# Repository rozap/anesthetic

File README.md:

# anaesthetic
r a c i n g

## Libraries
* https://github.com/avishorp/TM1637
* https://github.com/rlogiacco/CircularBuffer
* [RadioHead](http://www.airspayce.com/mikem/arduino/RadioHead/) (see setup, below)

## Docs
Oil pressure sensor: autometer 2242 https://www.autometer.com/sensor_specs

## RadioHead setup
RadioHead is the library for the LoRa modules. It runs on Aduino boards.
We use RadioHead 1.116, modified to work on 915MHz (there's a call to setFrequency hardcoded in the library source). A pre-modified version is included in this repo. To setup, unzip `RadioHead-anesthetic.zip` to `$HOME/Arduino/libraries`.

## Radio range test
There is a pair of Arduino sketches for a basic radio range test in `radio_range_test`. See instructions in sketch comments.

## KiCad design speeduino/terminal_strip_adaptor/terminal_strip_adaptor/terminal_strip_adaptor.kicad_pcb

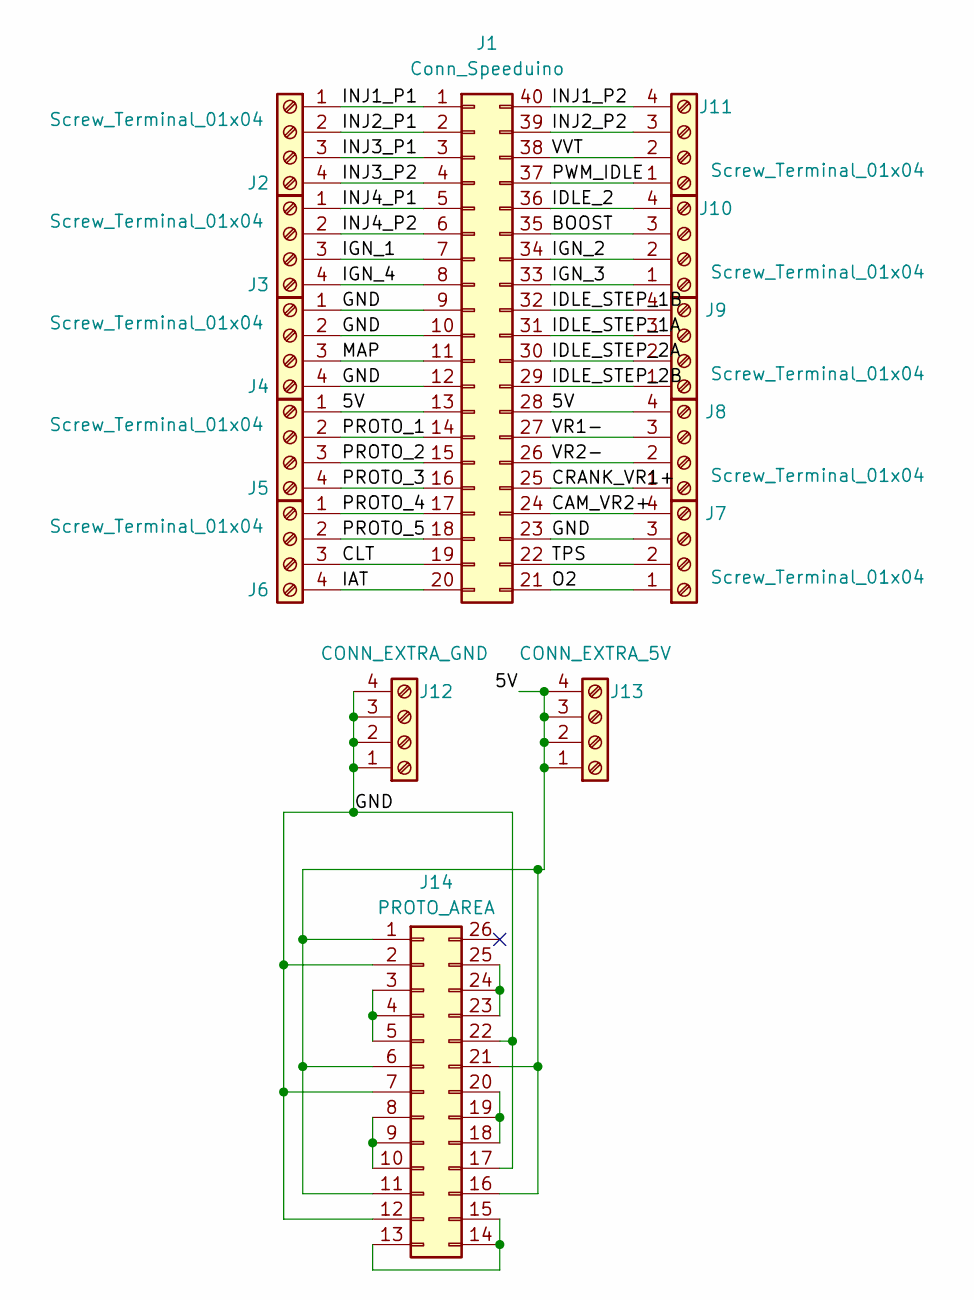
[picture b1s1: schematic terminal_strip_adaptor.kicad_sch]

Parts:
J1: Conn_Speeduino; PinSocket_2x20_P2.54mm_Vertical_CounterClockwise
J2, J3, J4, J5, J6, J7, J8, J9, J10, J11: Screw_Terminal_01x04; TerminalBlock_TE_282834-4_1x04_P2.54mm_Horizontal
J12: CONN_EXTRA_GND; TerminalBlock_TE_282834-4_1x04_P2.54mm_Horizontal
J13: CONN_EXTRA_5V; TerminalBlock_TE_282834-4_1x04_P2.54mm_Horizontal
J14: PROTO_AREA; PROTO_AREA_5x5_NO_OUTLINE

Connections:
/5V: J1.13, J1.28, J5.1, J8.4, J13.1, J13.2, J13.3, J13.4, J14.1, J14.6, J14.11, J14.16, J14.21
/BOOST: J1.35, J10.3
/CAM_VR2+: J1.24, J7.4
/CLT: J1.19, J6.3
/CRANK_VR1+: J1.25, J8.1
/GND: J1.9, J1.10, J1.12, J1.23, J4.1, J4.2, J4.4, J7.3, J12.1, J12.2, J12.3, J12.4, J14.2, J14.7, J14.12, J14.17, J14.22
/IAT: J1.20, J6.4
/IDLE_2: J1.36, J10.4
/IDLE_STEP_1A: J1.31, J9.3
/IDLE_STEP_1B: J1.32, J9.4
/IDLE_STEP_2A: J1.30, J9.2
/IDLE_STEP_2B: J1.29, J9.1
/IGN_1: J1.7, J3.3
/IGN_2: J1.34, J10.2
/IGN_3: J1.33, J10.1
/IGN_4: J1.8, J3.4
/INJ1_P1: J1.1, J2.1
/INJ1_P2: J1.40, J11.4
/INJ2_P1: J1.2, J2.2
/INJ2_P2: J1.39, J11.3
/INJ3_P1: J1.3, J2.3
/INJ3_P2: J1.4, J2.4
/INJ4_P1: J1.5, J3.1
/INJ4_P2: J1.6, J3.2
/MAP: J1.11, J4.3
/O2: J1.21, J7.1
/PROTO_1: J1.14, J5.2
/PROTO_2: J1.15, J5.3
/PROTO_3: J1.16, J5.4
/PROTO_4: J1.17, J6.1
/PROTO_5: J1.18, J6.2
/PWM_IDLE: J1.37, J11.1
/TPS: J1.22, J7.2
/VR1-: J1.27, J8.3
/VR2-: J1.26, J8.2
/VVT: J1.38, J11.2
unnamed: J14.3, J14.4, J14.5
unnamed: J14.8, J14.9, J14.10
unnamed: J14.13, J14.14, J14.15
unnamed: J14.18, J14.19, J14.20
unnamed: J14.23, J14.24, J14.25

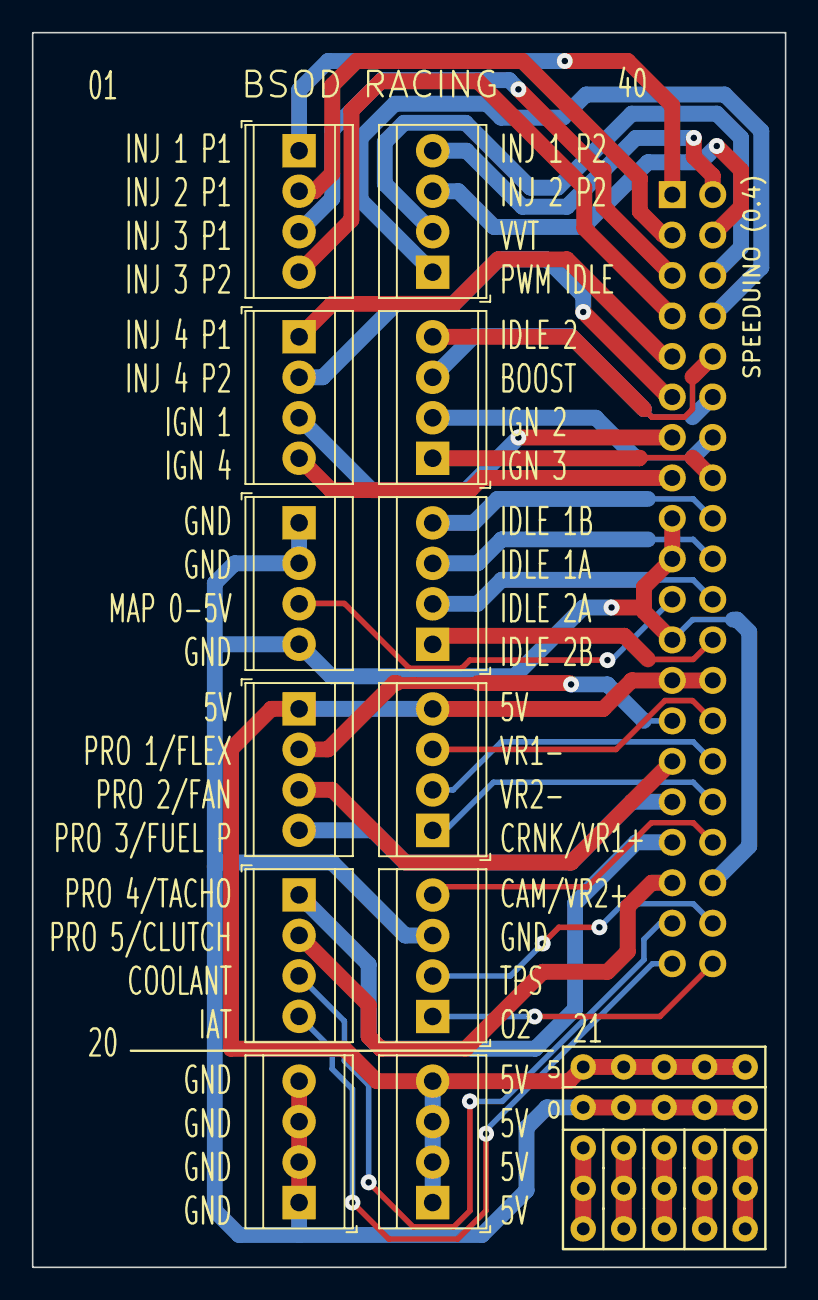
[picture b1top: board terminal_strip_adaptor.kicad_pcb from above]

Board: 2 copper layers, 47.2 x 77.5 mm, 14 parts (1 on the bottom side), 41 nets.

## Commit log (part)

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2020-04-01 make it so
2020-04-01 add docs
2020-04-01 how to markdown
2020-04-01 cleanup
2020-04-12 wtf??
2020-09-16 oops
2021-04-30 Add RadioHead lib and range test sketches.
2021-05-14 Transmit telemetry over radio and serial links.
2021-05-14 add server thing with framing
2021-05-14 send/recv
2021-05-14 more things
2021-06-12 Update sensor pins.
2021-06-12 Print digit test instead of FAIL because otherwise it's confusing.
2021-06-12 Radio: Pad numbers with zeros to 5 chars.
2021-06-18 Adjust sensor sample rate and window size.
2021-06-18 Faster startup.
2021-06-18 Lamp test on startup.
2021-06-18 Radio status in aux display.
2021-06-20 Switch to delayless sample/radio update scheme.
2021-06-20 Actually don't send radio messages all the time.
2021-06-20 I can't stop myself from making silly animations.
2021-06-21 Add vbat monitoring/radio message.
2021-06-21 Idiot light if vbat low.
2021-06-21 Attempt at computing rpm.
2021-06-21 Address some compilation warnings.
2021-06-21 Make RPM sampling work like other sensors.
2021-06-21 Send RPM via radio.
2021-06-21 Correct constant and typo in RPM conversion.
2021-06-21 Remove dead constant.
2021-06-21 Don't average RPM. It's causing precision problems, and it's already clean.
2021-06-21 Apply function invocation time offset to rpm period measurement.
2021-06-21 Increase sample rate.
2021-06-21 Filter out bogus RPM values (runt pulses).
2021-06-21 Stagger radio messages so they never block the main loop.
2021-06-23 Add base station.
2021-07-04 Add pitwall cli app
2021-07-08 refactor
2021-07-08 more efficient
2021-07-15 make serial work
2021-07-18 Fake oil temp
2021-07-18 more bin
2021-07-19 Correct RPM (rough).
2021-07-19 All telemetry info in one packet.
2021-07-19 RPM: Linear correction to match what we saw on the actual gauge.
2021-07-19 Coolant -> tenths of a psi
2021-07-19 Fix sample pitwall data.
2021-07-19 gitignore sw?
2021-07-19 pitwall: PSI graph scale -> 45 max
2021-07-19 DRY up rssi gauge code.
2021-07-19 pitwall: Only increment counter on actual received line.
2021-07-19 pitwall: ignore "init ok" message.
2021-07-19 pitwall: build release
2021-07-19 dash: fix oil temp reading (somewhat calibrated).
2021-07-19 telemetry_base_station: blink led on msg received.
2021-07-20 telemetry_base_station: Blinkenlights.
2021-07-21 dash: Add mission elapsed time in aux display + telemetry.
2021-07-21 Support MET in pitwall.
2021-07-21 Add shitty scrubbing and pause
2022-05-08 idk what this is
2022-05-30 dash: Update oil pressure calc for AutoMeter 2242 Resistive Transducer
2022-05-30 Dash: Support receiving `PIT:1` or `PIT:0` to control "PITS" driver msg.
2022-07-08 Dash: Read and send coolant temp (T_C) based on reading with 4.7k divider.
2022-07-10 dash: Fix VBAT scaling.
2022-07-10 Dash: Make oil temp actually report in F/10.
2022-07-10 Dash: Don't crash when sending telemetry packet (sprintf issue).
2022-08-09 make wiki.md
2022-10-09 dash: Don't trigger idiot light on oil temp if that sensor isn't installed.
2022-10-09 dash: blink idiot light.
2022-10-16 dash: disable clnt pressure sensor temporarily
2022-10-16 dash: framework for acknowledging found sensor issues.
2022-12-17 add speeduino stuff
2022-12-17 add speeduino pinout reference
2023-02-06 add misc physical part 3d models and cad files
2023-03-02 add monitor shade
2023-03-02 Add camera ups/shutdown circuit
2023-03-02 correct monitor shade dimensions slightly
2023-03-13 camera ups: upgrade kicad
2023-03-13 add ethernet switch and computer brackets, move model files around.
2023-03-15 add battery box
2023-03-15 Added notes and docs for camera system.
2023-03-15 moved files around cameras/
2023-03-15 update camera ip docs
2023-03-15 clean up ups circuit a bit
2023-03-17 Add 4 and 5 position switch guards (thanks Chris)
2023-03-18 Use 12v relay for UPS switch.
2023-03-18 Add 4 position switch guard (custom hole sizes + covers)
2023-03-18 ups: simplify, correct computer poweroff circuit
2023-03-18 UPS: more fixes
2023-03-23 Add lilliput monitor mount
2023-03-23 Add second part of monitor mount
2023-03-23 Add wooden board mount
2023-03-23 Add louvres
2023-03-24 cleanup of old cli pitwall software
2023-03-24 battery box
2023-03-25 real dims for battery box lid
2023-03-27 put onboard scripts under source control
2023-04-02 cams: remove overlay
2023-04-02 cams: reduce segment time
2023-04-02 cams: add fsck
2023-04-03 Add script for video combining.
2023-05-21 vr6 tune base
2023-08-21 add bumper mount blanking cap
2023-08-21 add speeduino screw terminal board
2023-08-21 add missing livery and graphics files
2023-08-21 add misc missing 3d models
2023-08-25 yeet
2023-08-29 Add GPS to dash
    * haven't tested this yet, but it compiles
    * GPS samples at 10hz, so we'll make it spit
    out messages like
    GPS:L<coord0|time0|speed0>L<coord1|time1|speed1>L<coord2|time2|speed2> etc
    * really want the time here for granularity, but it is
    uses a lot of bytes - unsure if it will cause issues rn
2023-09-24 add headset jack insulating washer
2023-09-24 pcb mounts
2023-10-16 sparse document livestream command
2023-10-16 I'm a dummy
2023-12-06 add BIG CLIPPY related models.
2024-01-11 Add stm32_dash
2024-02-25 stm32_dash: check for buffer overrun in pkt rec'v
2024-02-25 stm32_dash: Update firmware flashing instructions.
2024-02-25 stm32_dash: Alias Serial1, 2 to DebugSerial, SpeeduinoSerial
2024-02-25 stm32_dash: Don't wait for debug serial on boot - we can continue w/o it. Also it's no-op on stm32.
2024-02-25 an tune
2024-02-25 stm32_dash: If got packet bigger than buf, clear rx buffer.
2024-02-25 stm32_dash: Add capability to use mock data.
2024-03-26 current tune
2024-03-26 add stickers
2024-03-28 less fuel economy, more safe
2024-04-07 bootsplash
2024-04-07 Switch to another library. LoRa_STM32.
2024-04-07 fix RadioHead's broken platform workarounds.
2024-04-07 arduino-lora-stm32: Make use of LNA optional (RH95 compat).
2024-04-07 stm32: config radio to work with base station.
    Doesn't work right now because TFT steals the spi controller.
2024-04-07 first attempt at integrating radiohead & pull in our old radio code.
2024-04-07 docs for lora shield pinout
2024-04-07 import SX1278 lib from github.
2024-04-07 Use SPI port 2 to remove conflict with TFT. and YES, the removal of underscores is intentional here, but F me if I know why it's needed.
2024-04-07 Revert: arduino-lora-stm32: Support minimal RadioHead-style header.
2024-04-07 arduino-lora-stm32: Support minimal RadioHead-style header.
    - Send to broadcast address.
    - Reading packets... not done.
    This makes it work well enough for how we used RadioHead.
2024-04-07 progress on SX1278 arduino HAL
2024-04-07 optionally disable bootsplash (speeds up firmware download for debug).
2024-04-07 Add RadioHead lib (copy from old dash)
2024-04-07 Modify arduino-lora-stm32 lib to accept a custom SPIClass.
2024-04-07 losing my mind with SPI. nothing really works but at least it compiles lol
2024-04-07 arduino-lora-stm32: Copy over RadioHead's dumpRegisters for easier comparison.
2024-04-07 Add oil temp sensor reading code.
2024-04-07 Consolidate local sensor state into struct, to facilitate later selective TFT update logic.
    Also makes all local sensor updates centralized so they only get run once
    per frame, instead of however many times their value is needed in a frame.
    This makes the window time consistent, since we update the window on every
    read but don't factor in the timestamp of the data point.
2024-04-07 Implement lora telemetry using speeduino status.
2024-04-07 Support mock data for STM32 analog inputs.
2024-04-07 Add doc link for speeduino bitfields in telemetry.
2024-04-07 pin assignments drawing: remove blank margins
2024-04-07 pin assignments drawing: remove blank margins, try 2
2024-04-07 Use local timesource instead of Speeduino for MET (speeduino tops at 255s)
2024-04-07 Circuilar buffers out of sensors struct to make struct easier to diff
2024-04-07 Ratelimit telemetry packets to 1/sec.
2024-04-07 A newline is getting dropped somewhere, idk :shrug:
2024-04-07 Implement async telemetry TX. Else screen updates see ~400ms hitches.
2024-04-07 MM:SS MET display
2024-04-07 Only render status messages if there is a change.
2024-04-07 FPS counter.
2024-04-08 Link in a printf that actually supports floats... we have the resources.
2024-04-08 only render what changes. 4FPS -> 53FPS >:)
2024-04-08 imperceptibly speed up boot image blitting.
2024-04-08 Properly initialize I2C on boot.
2024-04-08 Tach lights start to show at 2k rpm not 3k.
2024-04-08 Avoid unneccesary tach light update.
2024-04-08 Add better mocks for main sensors.
2024-04-08 printf format strings are sharp, don't cut yourself.
2024-04-08 cuter mock data
2024-04-08 The "advance" field is int8_t from speeduino, not uint8_t.
2024-04-08 Reinstate idiot light.
2024-04-08 Move code around in main.cpp to make it at least somewhat navigable...
2024-04-08 Add gauge good/bad zone markers.
2024-04-08 Remove dead code.
2024-04-08 Warning message wording.
2024-04-08 Add visual separation between bar and zone marker.
2024-04-08 Clear tach lights if ECU isn't connected.
2024-04-08 Move configs to top of main.cpp
2024-04-08 Implement gps sending infra. Fills remaining pkt space with gps data.
2024-04-08 Do not treat low gas as an idiot condition. Our fuel gauge is not good.
2024-04-08 Docs for LED driver.
2024-04-08 Bump LoRa bandwidth from 125E3 to 250E3 to deal with all that GPS data.
2024-04-08 Actually push GPS data.
2024-04-09 Add Chris' dash enclosure.
2024-04-15 combine pinout docs
2024-04-18 Add a bunch of stm32 dash physical parts.
2024-04-18 Update tach pin assignments.
2024-04-18 More A E S T H E T I C tach boot animation.
2024-04-19 Calibrate oil T and fuel level sensors.
2024-04-19 add programming box 3d model
2024-04-20 Replace advance with oil T
2024-04-20 don't flash CEL when car off
2024-04-20 fix stuck red color in label text
2024-04-22 add a bunch of parts
2024-04-28 Extra debugging for GPS
2024-04-28 Transmit telemetry even when ECU drops out.
2024-04-28 Recalibrate fuel reading.
2024-04-28 v2 fuel spill funnel
2024-04-28 fix AV sync in camera videos
2024-04-29 Optionally skip truncated files.
2024-04-30 Split video files by session.
2024-06-05 Update fuel sender resistance.
2024-07-07 tweak fuel calibration
2024-08-21 Add fuel pressure to dash
2024-08-28 add headset wiring schematic
2024-09-29 mission shitshow svg
2025-01-06 wip on poting tune
2025-01-22 flow tester
2025-01-26 it starts but does not run
2025-02-10 latest tune
    ugh
2025-02-10 add gps can device
2025-02-12 wip on lora can
2025-02-12 do can over lora
    * more telemetry base station to can-devices
    * add cobs encoder
    * make it a pio project
    * work on gps and lora can devices
2025-02-23 splitting the devices up
2025-02-23 i do not understand embedded programming
    * why does this work
    * i got a impl on a branch (copied stm32_dash
    to can-devices folder) and it just booted but rendered
    a white screen. i copied all of those changes one by one
    back onto main, where the screen still worked, trying to find
    the bug, but then it just worked?
2025-02-23 it works
2025-02-23 debug
2025-02-23 add gps can device
    wip on lora can
    do can over lora
    * more telemetry base station to can-devices
    * add cobs encoder
    * make it a pio project
    * work on gps and lora can devices
2025-02-23 add current tuns; update can devices
2025-02-23 dash speaks CAN, it works-ish
2025-02-24 interrupt base can read
2025-02-24 things work; going to try dma
2025-02-24 wtf - why does dma not work
2025-03-02 more dash fixes
2025-03-02 add tft-dma-test can device, add fome-can-generator can device
2025-03-30 add knock counter to car display
2025-04-03 update tune
2025-04-04 update current tune
2025-04-20 bsod after 20 missed msgs (vs old 3)
2025-04-20 catch up commit: added conrod weighing adapter, stm32 pin assignments
2025-04-20 add aider files to gitignore
2025-04-20 add periodic CAN sensor message sending with configurable interval
2025-04-23 add brake design script
2025-04-23 cleanup
    * rm pitwall.rs
    * rm speeduino tune
    * mv lora stuff into folder
2025-04-24 updated tune
2025-04-29 numbers
2026-04-13 misc parts
2026-04-13 networking info
2026-04-14 feat: add push-to-talk application with gamepad support for Linux
2026-04-14 feat: add volume-based mute for Plantronics .Audio 646 DSP headset
